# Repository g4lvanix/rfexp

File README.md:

# RF experiments

This is a collection of RF experiments/peripherals for SDR.

The boards are designed to fit into an extruded aluminium case (Fischer Elektronik AKG 33 24 50).

Currently the repo contains hardware files for the following peripherals:
- universal back panel with power jack and SMA jack
- universal front panel with SMA jack and power indicator LED
- Coax line power injector/bias-tee
- Minicircuits PSA4-5043+ based LNA
- An active HF antenna based on the PA0RDT MiniWhip design

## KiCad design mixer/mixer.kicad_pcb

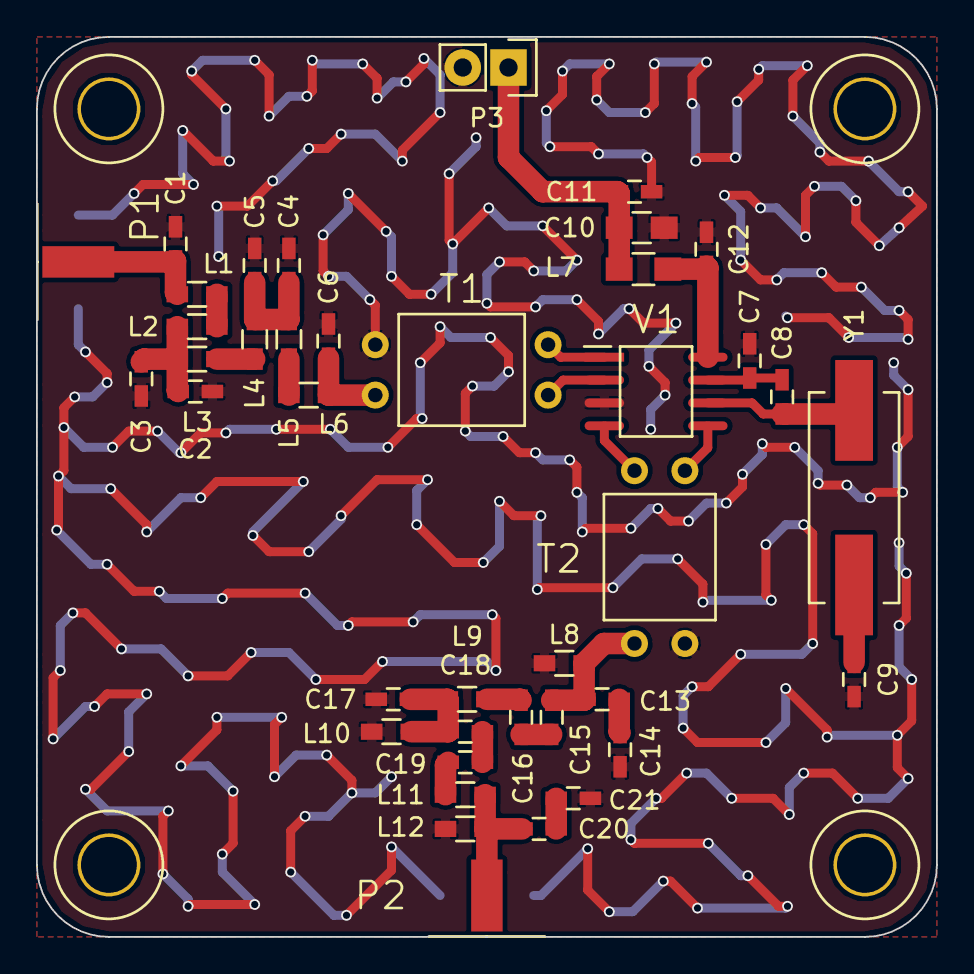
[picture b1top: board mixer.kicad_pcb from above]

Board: 2 copper layers, 50.0 x 50.0 mm, 40 parts (0 on the bottom side), 26 nets.

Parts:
C1, C3, C5, C6: 68p; C_0603_HandSoldering
C2, C4: 220p; C_0603_HandSoldering
C7, C8: 22p; C_0603_HandSoldering
C9: 10p; C_0603_HandSoldering
C10: 1u; C_0805_HandSoldering
C11: 100n; C_0603_HandSoldering
C12: 10n; C_0603_HandSoldering
C13, C17, C20: 330p; C_0603_HandSoldering
C14, C16, C19, C21: 150p; C_0603_HandSoldering
C15, C18: 47p; C_0603_HandSoldering
L1, L5: 33n; R_0603_HandSoldering
L2, L6: 470n; R_0603_HandSoldering
L3, L9, L11: 680n; R_0603_HandSoldering
L4: 100n; R_0603_HandSoldering
L7: 4u7; R_0805_HandSoldering
L8, L12: 220n; R_0603_HandSoldering
L10: 68n; R_0603_HandSoldering
P1: RF; SMA-BU-P_EdgeMount
P2: IF; SMA-BU-P_EdgeMount
P3: POWER; Pin_Header_Straight_1x02
T1: 2:11; BALUN-BINOCULAR
T2: 11:2; BALUN-BINOCULAR
V1: SA602A; SO8
Y1: 25MHz; Crystal_HC49-SD_SMD

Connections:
+5V: C10.1, C11.1, L7.1, P3.1
/IF: C20.2, L11.2, L12.1, P2.1
/RF: C1.1, L1.1, P1.1
GND: C1.2, C2.2, C3.1, C4.2, C5.1, C6.2, C7.1, C9.2, C10.2, C11.2, C12.2, C14.1, C17.1, C21.1, L8.2, L10.2, L12.2, P1.2, P2.2, P3.2, T1.2, T2.3, V1.3
unnamed: C2.1, C3.2, L2.2, L3.1
unnamed: C4.1, C5.2, L4.2, L5.1
unnamed: C6.1, L6.2, T1.1
unnamed: C7.2, C8.1, V1.7
unnamed: C8.2, V1.6, Y1.2
unnamed: C9.1, Y1.1
unnamed: C12.1, L7.2, V1.8
unnamed: C13.1, C14.2
unnamed: C13.2, C15.1, L8.1, T2.4
unnamed: C15.2, C16.1
unnamed: C16.2, L9.1
unnamed: C17.2, C18.1, L9.2, L10.1
unnamed: C18.2, C19.1
unnamed: C19.2, L11.1
unnamed: C20.1, C21.2
unnamed: L1.2, L2.1
unnamed: L3.2, L4.1
unnamed: L5.2, L6.1
unnamed: T1.3, V1.1
unnamed: T1.4, V1.2
unnamed: T2.1, V1.4
unnamed: T2.2, V1.5

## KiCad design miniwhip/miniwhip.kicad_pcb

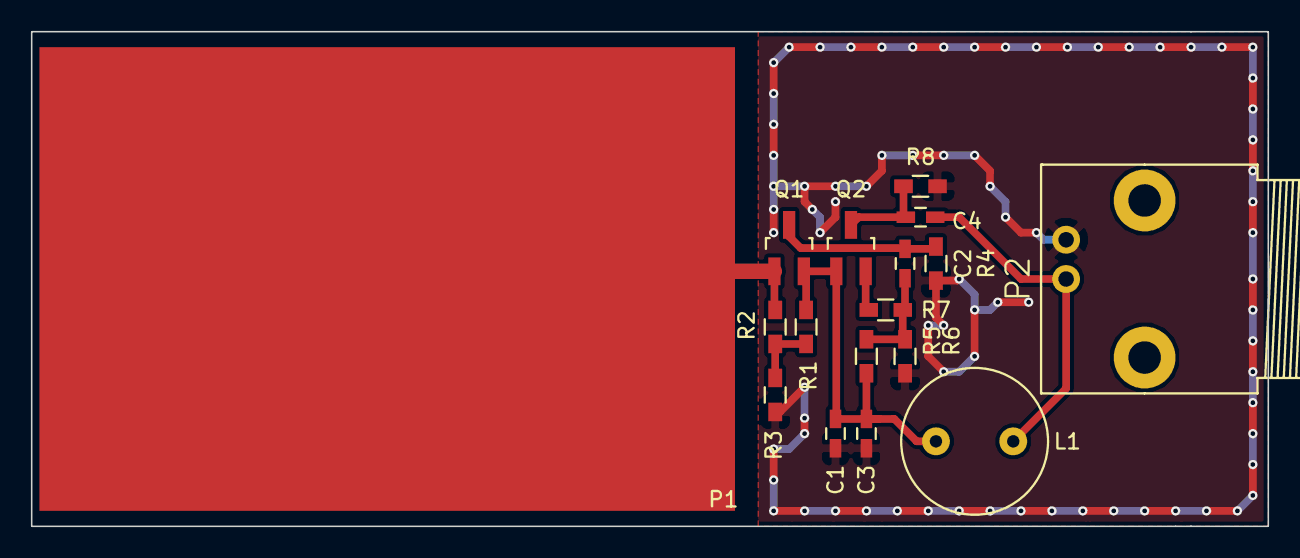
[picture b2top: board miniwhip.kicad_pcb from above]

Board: 2 copper layers, 80.0 x 32.0 mm, 17 parts (0 on the bottom side), 9 nets.

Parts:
C1, C2, C3, C4: 100nF; C_0603_HandSoldering
L1: 470uH; FASTRON-09P
P1: MINIWHIP
P2: BNC; BNC_horizontal
Q1: MMBF5485; SOT-23_Handsoldering
Q2: BFR92; SOT-23_Handsoldering
R1, R2, R3: 1M; R_0603_HandSoldering
R4: 680; R_0603_HandSoldering
R5: 2k2; R_0603_HandSoldering
R6: 10k; R_0603_HandSoldering
R7: 47; R_0603_HandSoldering
R8: 220; R_0603_HandSoldering

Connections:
/PROBE: P1.1, Q1.1, R2.1
/P_IN: C4.1, L1.2, P2.1
GND: C1.2, C3.1, P2.2, R3.2, R4.2, R6.2, R8.2
unnamed: C2.1, R5.2, R6.1, R7.2
unnamed: C2.2, Q1.3, R4.1
unnamed: C4.2, Q2.3, R8.1
unnamed: Q2.2, R7.1
unnamed: R1.2, R2.2, R3.1
VCC: C1.1, C3.2, L1.1, Q1.2, Q2.1, R1.1, R5.1

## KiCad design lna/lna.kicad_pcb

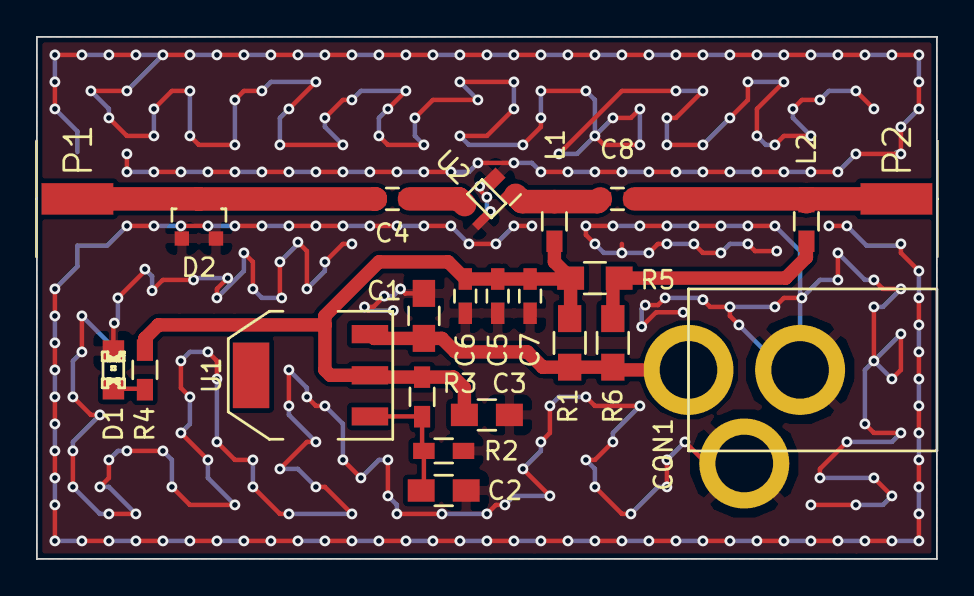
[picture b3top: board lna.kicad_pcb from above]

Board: 2 copper layers, 50.0 x 29.0 mm, 23 parts (0 on the bottom side), 10 nets.

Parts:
C1, C2, C3: 1uF; C_0805_HandSoldering
C4, C7, C8: 100pF; C_0603_HandSoldering
C5: 10nF; C_0603_HandSoldering
C6: 1nF; C_0603_HandSoldering
CON1: BARREL_JACK; JACK_DC
D1: POWER; LED-0805
D2: BAV99; SOT-23
L1: 3.3uH; R_0603_HandSoldering
L2: 10uH; R_0603_HandSoldering
P1: ANT; SMA-BU-P_EdgeMount
P2: RX; SMA-BU-P_EdgeMount
R1, R5, R6: 0; R_0805_HandSoldering
R2: 330; R_0603_HandSoldering
R3: 220; R_0603_HandSoldering
R4: 1k; R_0603_HandSoldering
U1: LM317AEMP; SOT-223
U2: PSA4-5043+; SOT-343

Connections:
/ANT: C4.2, D2.3, P1.1
/DCIN: C1.1, CON1.1, R1.2, R6.1, U1.3
/RFIN: C4.1, U2.3
/RFOUT: C8.2, L1.2, U2.1
/RX: C8.1, L2.2, P2.1
GND: C1.2, C2.2, C3.2, C5.2, C6.2, C7.2, CON1.2, CON1.3, D1.1, D2.1, D2.2, P1.2, P2.2, R2.2, U2.2, U2.4
unnamed: C2.1, R2.1, R3.2, U1.1
unnamed: D1.2, R4.2
unnamed: L2.1, R5.1, R6.2
VCC: C3.1, C5.1, C6.1, C7.1, L1.1, R1.1, R3.1, R4.1, R5.2, U1.2

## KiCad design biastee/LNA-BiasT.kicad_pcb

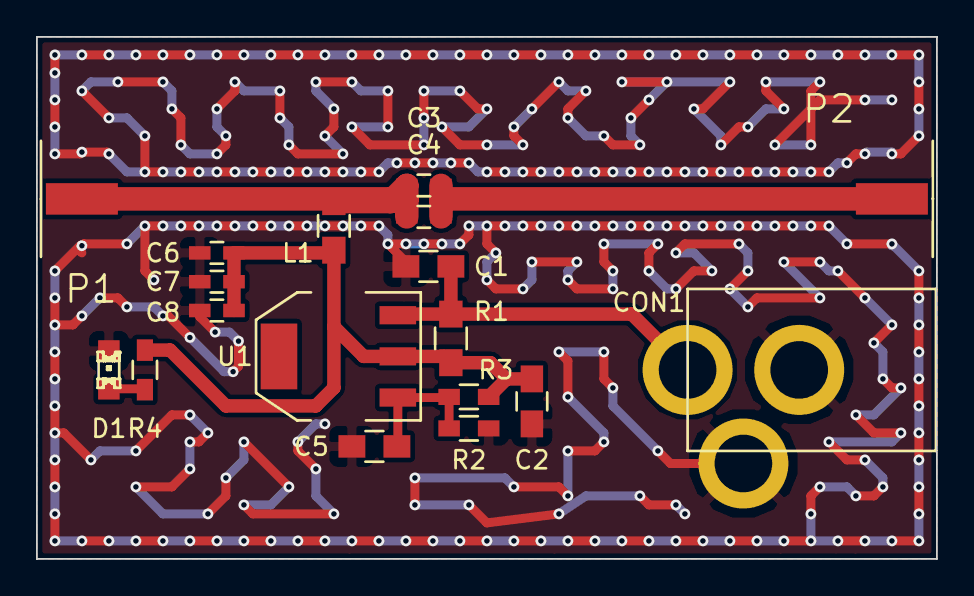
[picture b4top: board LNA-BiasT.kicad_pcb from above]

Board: 2 copper layers, 50.0 x 29.0 mm, 18 parts (0 on the bottom side), 7 nets.

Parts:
C1, C2, C5: 1uF; C_0805_HandSoldering
C3, C7: 1nF; C_0603_HandSoldering
C4, C8: 100pF; C_0603_HandSoldering
C6: 10nF; C_0603_HandSoldering
CON1: DC; JACK_DC
D1: PWR; LED-0805
L1: 10uH; R_0805_HandSoldering
P1: ANT; SMA-BU-P_EdgeMount
P2: RX; SMA-BU-P_EdgeMount
R1: 0; R_0805_HandSoldering
R2: R; R_0603_HandSoldering
R3: 220; R_0603_HandSoldering
R4: 1k; R_0603_HandSoldering
U1: LM317AEMP; SOT-223

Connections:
/DCIN: C1.1, CON1.1, R1.1, U1.3
/REGOUT: C2.1, C6.1, C7.1, C8.1, L1.1, R1.2, R3.1, R4.2, U1.2
/RF: C3.2, C4.1, P2.1
/RFDC: C3.1, C4.2, L1.2, P1.1
GND: C1.2, C2.2, C5.2, C6.2, C7.2, C8.2, CON1.2, CON1.3, D1.1, P1.2, P2.2, R2.2
unnamed: C5.1, R2.1, R3.2, U1.1
unnamed: D1.2, R4.1

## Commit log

2015-06-07 added bias tee backpanel
2015-06-07 added bias-tee files
2015-06-07 added LNA front panel
2015-06-07 added more decoupling capacitors
2015-06-07 added PSA4-5043+ based LNA
2015-07-31 added minwhip antenna design
2015-08-05 changed silksreen slightly
2015-10-04 added upconverter
